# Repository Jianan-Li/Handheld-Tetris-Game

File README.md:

# Handheld-Tetris-Game

Click <a href="http://www.jianan.li/handheld-tetris-game">here</a> for more info on this project.

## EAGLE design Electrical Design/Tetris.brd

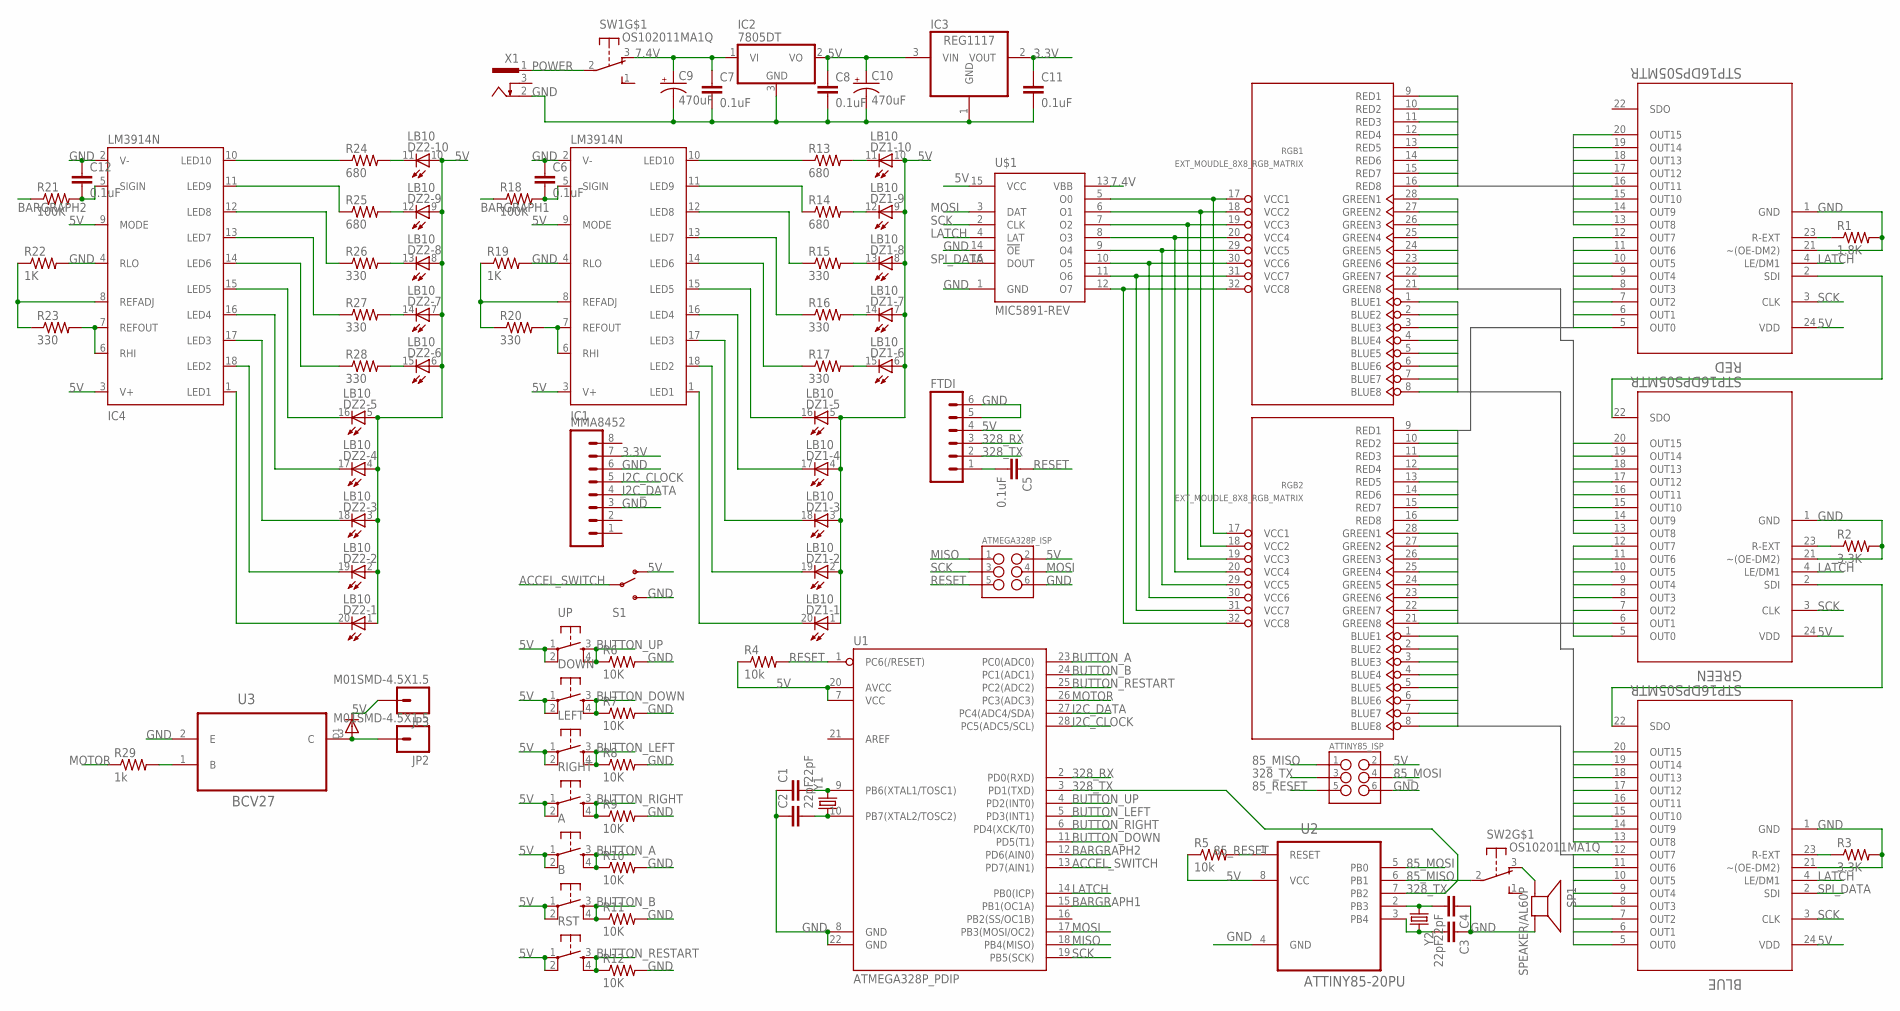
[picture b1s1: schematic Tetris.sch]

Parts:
A: TAC_SWITCHPTH; TACTILE-PTH
ATMEGA328P_ISP: M03X22X3_SILK_SM; 2X3
ATTINY85_ISP: M03X22X3_SILK_SM; 2X3
B: TAC_SWITCHPTH; TACTILE-PTH
BLUE: STP16DPS05MTR; SOIC127P1032X265-24N
C1, C2, C3, C4: 22pF; 0805
C5, C6, C7, C8, C11, C12: 0.1uF; 0805
C9, C10: 470uF; PANASONIC_D
D1: DIODESMA; SMADIODE
DOWN: TAC_SWITCHPTH; TACTILE-PTH
DZ1, DZ2: LB10
FTDI: M06LOCK; 1X06_LOCK
GREEN: STP16DPS05MTR; SOIC127P1032X265-24N
IC1, IC4: LM3914N; DIL18
IC2: 7805DT; TO252
IC3: REG1117; SOT223
JP2, JP3: M01SMD-4.5X1.5; PAD-1.5X4.5
LEFT: TAC_SWITCHPTH; TACTILE-PTH
MMA8452: M08LOCK; 1X08_LOCK
R1: 1.8K; 0805
R2, R3: 3.3K; 0805
R4, R5: 10k; 0805
R6, R7, R8, R9, R10, R11, R12: 10K; 0805
R13, R14, R24, R25: 680; 0805
R15, R16, R17, R20, R23, R26, R27, R28: 330; 0805
R18, R21: 100K; 0805
R19, R22: 1K; 0805
R29: 1k; 0805
RED: STP16DPS05MTR; SOIC127P1032X265-24N
RGB1, RGB2: EXT_MOUDLE_8X8_RGB_MATRIX
RIGHT: TAC_SWITCHPTH; TACTILE-PTH
RST: TAC_SWITCHPTH; TACTILE-PTH
S1: SWITCH-SPDTPTH_LOCK; SWITCH-SPDT_LOCK.007S
SP1: SPEAKER/AL60P; AL60P
SW1, SW2: OS102011MA1Q
U1: ATMEGA328P_PDIP; DIL28-3
U2: ATTINY85-20PU; DIP254P762X533-8
U3: BCV27; SOT95P230X93-3N
U$1: MIC5891-REV; DIL16
UP: TAC_SWITCHPTH; TACTILE-PTH
X1: 733989-5
Y1, Y2: CRYSTALHC49US; HC49US

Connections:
3.3V: C11.1, IC3.2 (VOUT), MMA8452.7
5V: A.1, A.2, ATMEGA328P_ISP.2, ATTINY85_ISP.2, B.1, B.2, BLUE.24 (VDD), C8.1, C10.+, D1.C, DOWN.1, DOWN.2, DZ1.1 (A), DZ1.2 (A), DZ1.3 (A), DZ1.4 (A), DZ1.5 (A), DZ1.6 (A), DZ1.7 (A), DZ1.8 (A), DZ1.9 (A), DZ1.10 (A), DZ2.1 (A), DZ2.2 (A), DZ2.3 (A), DZ2.4 (A), DZ2.5 (A), DZ2.6 (A), DZ2.7 (A), DZ2.8 (A), DZ2.9 (A), DZ2.10 (A), FTDI.4, GREEN.24 (VDD), IC1.3 (V+), IC1.9 (MODE), IC2.2 (VO), IC3.3 (VIN), IC4.3 (V+), IC4.9 (MODE), JP3.P$1, LEFT.1, LEFT.2, R4.1, R5.1, RED.24 (VDD), RIGHT.1, RIGHT.2, RST.1, RST.2, S1.1 (O), U1.7 (VCC), U1.20 (AVCC), U2.8 (VCC), U$1.15 (VCC), UP.1, UP.2
7.4V: C7.1, C9.+, IC2.1 (VI), SW1.3 (O), U$1.13 (VBB)
85_MISO: ATTINY85_ISP.1, SW2.2, U2.6 (PB1)
85_MOSI: ATTINY85_ISP.4, U2.5 (PB0)
85_RESET: ATTINY85_ISP.5, R5.2, U2.1 (RESET)
328_RX: FTDI.3, U1.2 (PD0(RXD))
328_TX: ATTINY85_ISP.3, FTDI.2, U1.3 (PD1(TXD)), U2.7 (PB2)
ACCEL_SWITCH: S1.2, U1.13 (PD7(AIN1))
BARGRAPH1: R18.1, U1.15 (PB1(OC1A))
BARGRAPH2: R21.1, U1.12 (PD6(AIN0))
BLUE1: BLUE.20 (OUT15), RGB1.8 (BLUE8)
BLUE2: BLUE.19 (OUT14), RGB1.7 (BLUE7)
BLUE3: BLUE.18 (OUT13), RGB1.6 (BLUE6)
BLUE4: BLUE.17 (OUT12), RGB1.5 (BLUE5)
BLUE5: BLUE.16 (OUT11), RGB1.4 (BLUE4)
BLUE6: BLUE.15 (OUT10), RGB1.3 (BLUE3)
BLUE7: BLUE.14 (OUT9), RGB1.2 (BLUE2)
BLUE8: BLUE.13 (OUT8), RGB1.1 (BLUE1)
BLUE9: BLUE.12 (OUT7), RGB2.8 (BLUE8)
BLUE10: BLUE.11 (OUT6), RGB2.7 (BLUE7)
BLUE11: BLUE.10 (OUT5), RGB2.6 (BLUE6)
BLUE12: BLUE.9 (OUT4), RGB2.5 (BLUE5)
BLUE13: BLUE.8 (OUT3), RGB2.4 (BLUE4)
BLUE14: BLUE.7 (OUT2), RGB2.3 (BLUE3)
BLUE15: BLUE.6 (OUT1), RGB2.2 (BLUE2)
BLUE16: BLUE.5 (OUT0), RGB2.1 (BLUE1)
BUTTON_A: A.3, A.4, R10.1, U1.23 (PC0(ADC0))
BUTTON_B: B.3, B.4, R11.1, U1.24 (PC1(ADC1))
BUTTON_DOWN: DOWN.3, DOWN.4, R7.1, U1.11 (PD5(T1))
BUTTON_LEFT: LEFT.3, LEFT.4, R8.1, U1.5 (PD3(INT1))
BUTTON_RESTART: R12.1, RST.3, RST.4, U1.25 (PC2(ADC2))
BUTTON_RIGHT: R9.1, RIGHT.3, RIGHT.4, U1.6 (PD4(XCK/T0))
BUTTON_UP: R6.1, U1.4 (PD2(INT0)), UP.3, UP.4
GND: ATMEGA328P_ISP.6, ATTINY85_ISP.6, BLUE.1 (GND), BLUE.21 (~(OE-DM2)), C1.1, C2.1, C3.1, C4.1, C6.1, C7.2, C8.2, C9.-, C10.-, C11.2, C12.1, FTDI.5, FTDI.6, GREEN.1 (GND), GREEN.21 (~(OE-DM2)), IC1.2 (V-), IC1.4 (RLO), IC2.3 (GND), IC3.1 (GND), IC4.2 (V-), IC4.4 (RLO), MMA8452.3, MMA8452.6, R1.2, R2.2, R3.2, R6.2, R7.2, R8.2, R9.2, R10.2, R11.2, R12.2, R19.2, R22.2, RED.1 (GND), RED.21 (~(OE-DM2)), S1.3 (S), SP1.2 (-), U1.8 (GND), U1.22 (GND), U2.4 (GND), U3.2 (E), U$1.1 (GND), U$1.14 (!OE), X1.2
GREEN1: GREEN.20 (OUT15), RGB1.21 (GREEN8)
GREEN2: GREEN.19 (OUT14), RGB1.22 (GREEN7)
GREEN3: GREEN.18 (OUT13), RGB1.23 (GREEN6)
GREEN4: GREEN.17 (OUT12), RGB1.24 (GREEN5)
GREEN5: GREEN.16 (OUT11), RGB1.25 (GREEN4)
GREEN6: GREEN.15 (OUT10), RGB1.26 (GREEN3)
GREEN7: GREEN.14 (OUT9), RGB1.27 (GREEN2)
GREEN8: GREEN.13 (OUT8), RGB1.28 (GREEN1)
GREEN9: GREEN.12 (OUT7), RGB2.21 (GREEN8)
GREEN10: GREEN.11 (OUT6), RGB2.22 (GREEN7)
GREEN11: GREEN.10 (OUT5), RGB2.23 (GREEN6)
GREEN12: GREEN.9 (OUT4), RGB2.24 (GREEN5)
GREEN13: GREEN.8 (OUT3), RGB2.25 (GREEN4)
GREEN14: GREEN.7 (OUT2), RGB2.26 (GREEN3)
GREEN15: GREEN.6 (OUT1), RGB2.27 (GREEN2)
GREEN16: GREEN.5 (OUT0), RGB2.28 (GREEN1)
I2C_CLOCK: MMA8452.5, U1.28 (PC5(ADC5/SCL))
I2C_DATA: MMA8452.4, U1.27 (PC4(ADC4/SDA))
LATCH: BLUE.4 (LE/DM1), GREEN.4 (LE/DM1), RED.4 (LE/DM1), U1.14 (PB0(ICP)), U$1.4 (LAT)
MISO: ATMEGA328P_ISP.1, U1.18 (PB4(MISO))
MOSI: ATMEGA328P_ISP.4, U1.17 (PB3(MOSI/OC2)), U$1.3 (DAT)
MOTOR: R29.1, U1.26 (PC3(ADC3))
unnamed: R1.1, RED.23 (R-EXT)
unnamed: RGB1.18 (VCC2), RGB2.18 (VCC2), U$1.6 (O1)
unnamed: RGB1.19 (VCC3), RGB2.19 (VCC3), U$1.7 (O2)
unnamed: RGB1.20 (VCC4), RGB2.20 (VCC4), U$1.8 (O3)
unnamed: RGB1.29 (VCC5), RGB2.29 (VCC5), U$1.9 (O4)
unnamed: RGB1.30 (VCC6), RGB2.30 (VCC6), U$1.10 (O5)
unnamed: RGB1.31 (VCC7), RGB2.31 (VCC7), U$1.11 (O6)
unnamed: RGB1.32 (VCC8), RGB2.32 (VCC8), U$1.12 (O7)
unnamed: C5.2, FTDI.1
unnamed: DZ1.15 (C), R17.2
unnamed: C1.2, U1.9 (PB6(XTAL1/TOSC1)), Y1.2
unnamed: C2.2, U1.10 (PB7(XTAL2/TOSC2)), Y1.1
unnamed: C3.2, U2.3 (PB4), Y2.2
unnamed: C4.2, U2.2 (PB3), Y2.1
unnamed: DZ1.14 (C), R16.2
unnamed: DZ1.13 (C), R15.2
unnamed: GREEN.22 (SDO), RED.2 (SDI)
unnamed: GREEN.23 (R-EXT), R2.1
unnamed: RGB1.17 (VCC1), RGB2.17 (VCC1), U$1.5 (O0)
unnamed: DZ1.12 (C), R14.2
unnamed: DZ1.11 (C), R13.2
unnamed: BLUE.22 (SDO), GREEN.2 (SDI)
unnamed: IC1.10 (LED10), R13.1
unnamed: BLUE.23 (R-EXT), R3.1
unnamed: IC1.11 (LED9), R14.1
unnamed: IC1.12 (LED8), R15.1
unnamed: IC1.13 (LED7), R16.1
unnamed: IC1.14 (LED6), R17.1
unnamed: DZ1.16 (C), IC1.15 (LED5)
unnamed: DZ1.17 (C), IC1.16 (LED4)
unnamed: DZ1.18 (C), IC1.17 (LED3)
unnamed: DZ1.19 (C), IC1.18 (LED2)
unnamed: DZ1.20 (C), IC1.1 (LED1)
unnamed: C6.2, IC1.5 (SIGIN), R18.2
unnamed: IC1.8 (REFADJ), R19.1, R20.1
unnamed: IC1.6 (RHI), IC1.7 (REFOUT), R20.2
unnamed: IC4.11 (LED9), R25.1
unnamed: IC4.12 (LED8), R26.1
unnamed: IC4.13 (LED7), R27.1
unnamed: IC4.14 (LED6), R28.1
unnamed: DZ2.16 (C), IC4.15 (LED5)
unnamed: DZ2.17 (C), IC4.16 (LED4)
unnamed: DZ2.18 (C), IC4.17 (LED3)
unnamed: DZ2.19 (C), IC4.18 (LED2)
unnamed: DZ2.20 (C), IC4.1 (LED1)
unnamed: C12.2, IC4.5 (SIGIN), R21.2
unnamed: IC4.8 (REFADJ), R22.1, R23.1
unnamed: IC4.6 (RHI), IC4.7 (REFOUT), R23.2
unnamed: IC4.10 (LED10), R24.1
unnamed: DZ2.15 (C), R28.2
unnamed: DZ2.14 (C), R27.2
unnamed: DZ2.13 (C), R26.2
unnamed: DZ2.12 (C), R25.2
unnamed: DZ2.11 (C), R24.2
unnamed: R29.2, U3.1 (B)
unnamed: D1.A, JP2.P$1, U3.3 (C)
unnamed: SP1.1 (+), SW2.3 (O)
POWER: SW1.2, X1.1
RED1: RED.20 (OUT15), RGB1.16 (RED8)
RED2: RED.19 (OUT14), RGB1.15 (RED7)
RED3: RED.18 (OUT13), RGB1.14 (RED6)
RED4: RED.17 (OUT12), RGB1.13 (RED5)
RED5: RED.16 (OUT11), RGB1.12 (RED4)
RED6: RED.15 (OUT10), RGB1.11 (RED3)
RED7: RED.14 (OUT9), RGB1.10 (RED2)
RED8: RED.13 (OUT8), RGB1.9 (RED1)
RED9: RED.12 (OUT7), RGB2.16 (RED8)
RED10: RED.11 (OUT6), RGB2.15 (RED7)
RED11: RED.10 (OUT5), RGB2.14 (RED6)
RED12: RED.9 (OUT4), RGB2.13 (RED5)
RED13: RED.8 (OUT3), RGB2.12 (RED4)
RED14: RED.7 (OUT2), RGB2.11 (RED3)
RED15: RED.6 (OUT1), RGB2.10 (RED2)
RED16: RED.5 (OUT0), RGB2.9 (RED1)
RESET: ATMEGA328P_ISP.5, C5.1, R4.2, U1.1 (PC6(/RESET))
SCK: ATMEGA328P_ISP.3, BLUE.3 (CLK), GREEN.3 (CLK), RED.3 (CLK), U1.19 (PB5(SCK)), U$1.2 (CLK)
SPI_DATA: BLUE.2 (SDI), U$1.16 (DOUT)

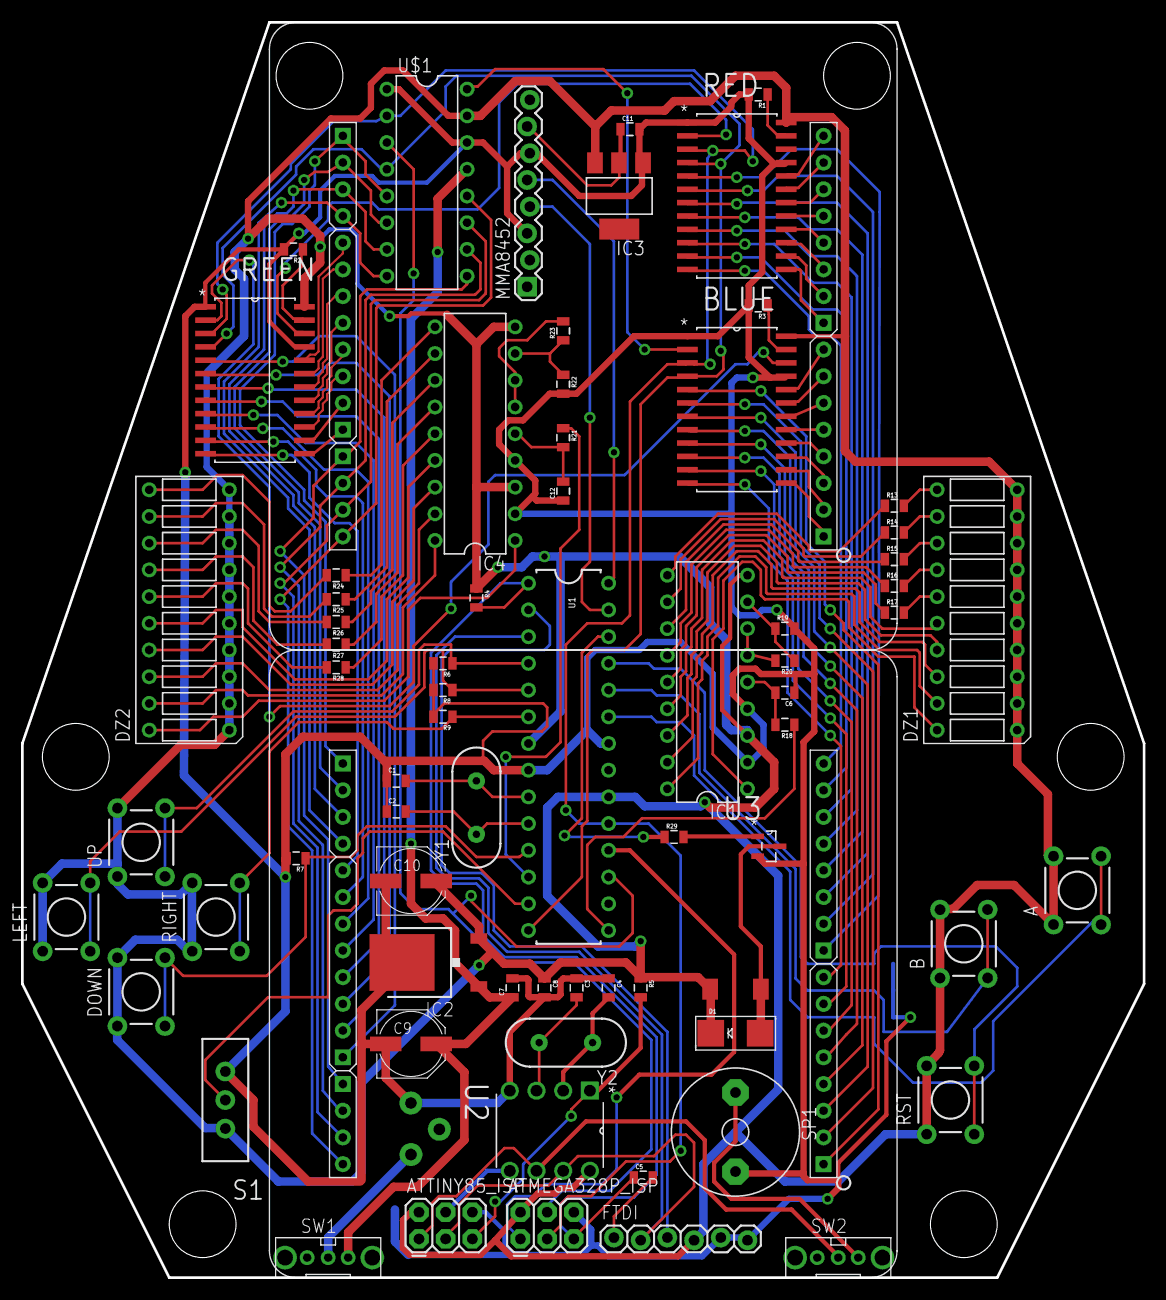
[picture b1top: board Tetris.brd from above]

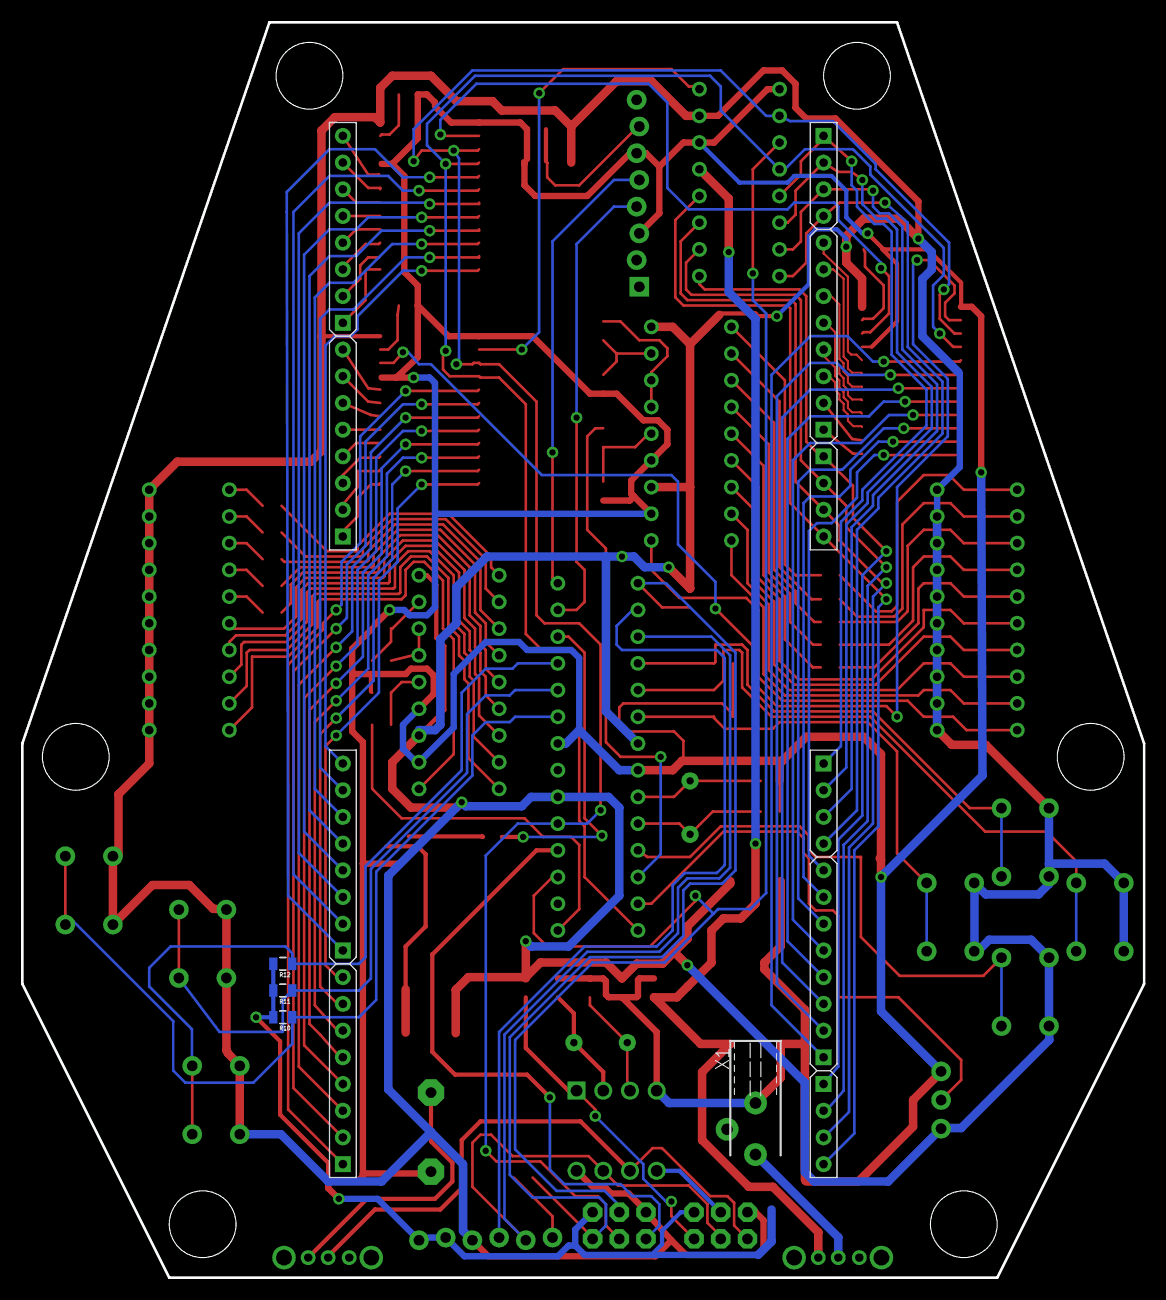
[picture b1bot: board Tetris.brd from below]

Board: 2 copper layers, 106.7 x 119.4 mm, 77 parts (4 on the bottom side), 134 nets.

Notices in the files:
parts and their libraries:
Edeca.net: This is v1 and is licensed under the Creative Commons (Attribution-Non-Commercial-Share Alike 2.0 UK)
SparkFun-Connectors: Licensing: CC v3.0 Share-Alike You are welcome to use this library for commercial purposes.
